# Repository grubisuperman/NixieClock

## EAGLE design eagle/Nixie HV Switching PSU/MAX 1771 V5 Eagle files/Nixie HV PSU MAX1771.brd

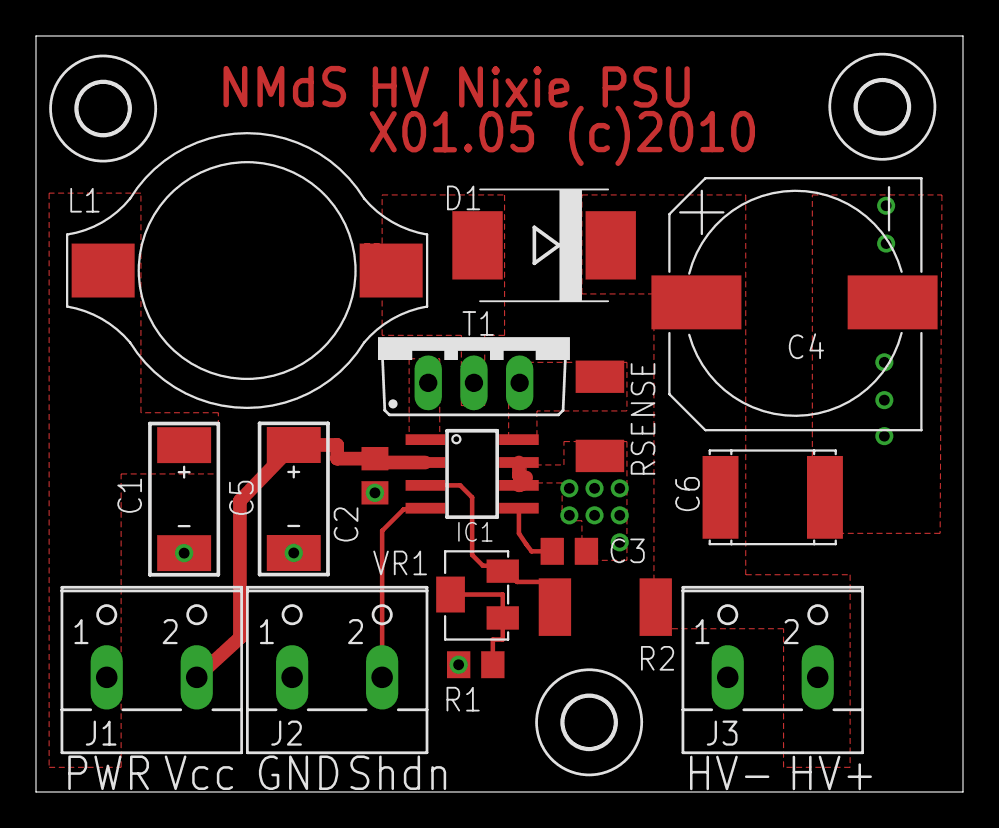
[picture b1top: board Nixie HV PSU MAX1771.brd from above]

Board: 2 copper layers, 51.5 x 42.0 mm, 20 parts (0 on the bottom side), 11 nets.

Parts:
C1: 100uF,35V; C-EIA-7343
C2, C3: 100n; C0805
C4: 4u7,250V; NICHICON-UJ-12
C5: 10uF,25V; C-EIA-7343
C6: 100n,250V; C2420
D1: ES2F; SMC
IC1: MAX1771ESA; SO-8
J1, J2, J3: SCREW-2-02
L1: 100uH; L-B82479
R1: 10K; R0805
R2: 1M5; R2512
RSENSE: 0R050; R2010
T1: IRF644PBF; TO220BV
U$2, U$3, U$4: 2,8
VR1: 5K; BOURNS-3214W

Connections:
DGND: C1.-, C2.2, C3.2, C4.1, C5.-, C6.P$2, IC1.6, IC1.7, J2.1, J3.1, R1.1, RSENSE.1
EXT: IC1.1, T1.G
unnamed: IC1.8, RSENSE.2, T1.S
unnamed: R1.2, VR1.1, VR1.2
unnamed: IC1.3, R2.1, VR1.3
unnamed: D1.A, L1.P$2, T1.D
unnamed: C3.1, IC1.5
PWR: C1.+, J1.1, L1.P$1
SHDN: IC1.4, J2.2
VCC: C2.1, C5.+, IC1.2, J1.2
VOUT: C4.2, C6.P$1, D1.C, J3.2, R2.2

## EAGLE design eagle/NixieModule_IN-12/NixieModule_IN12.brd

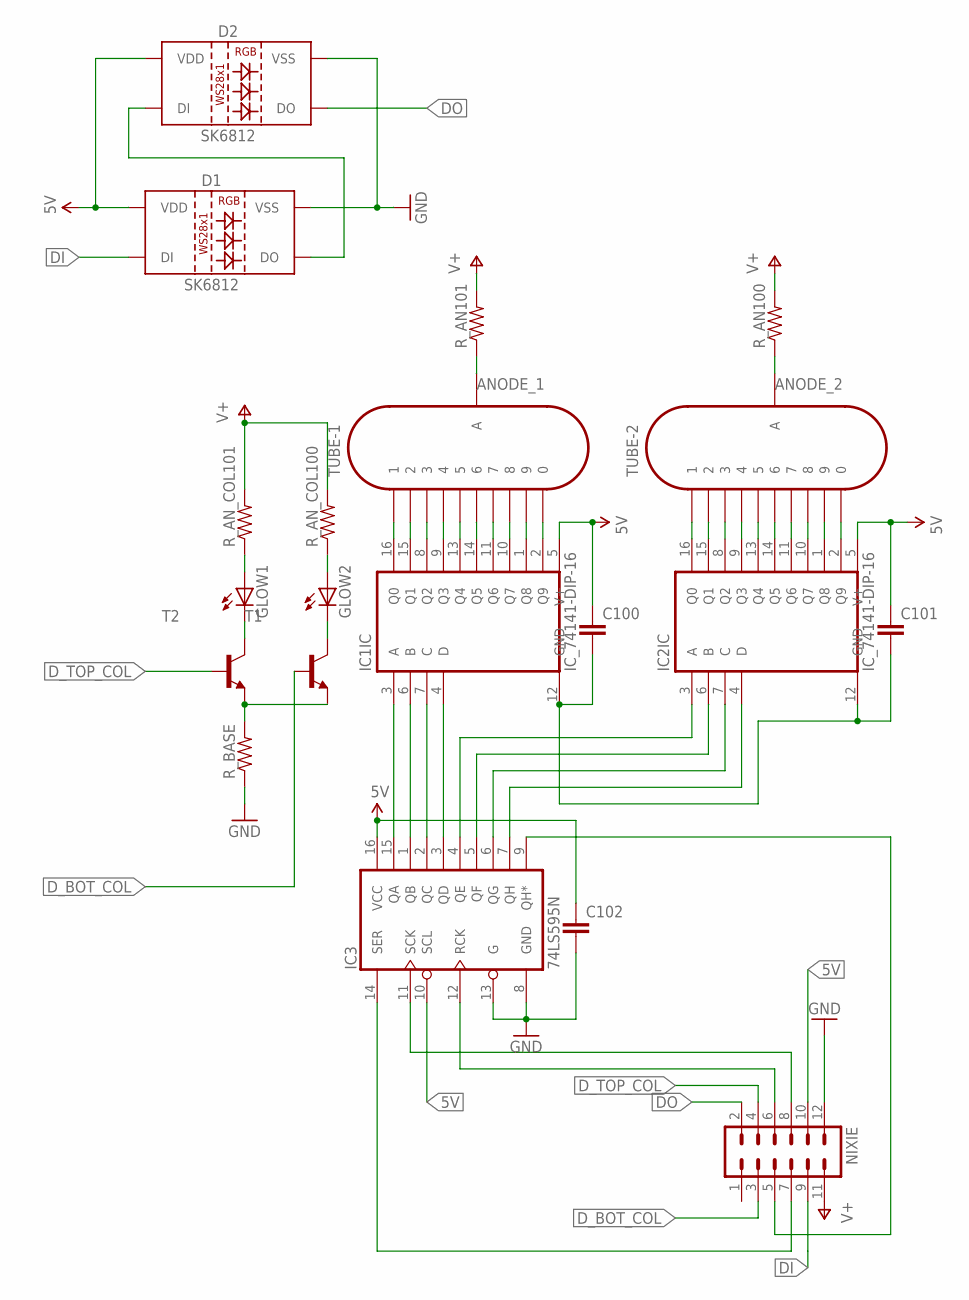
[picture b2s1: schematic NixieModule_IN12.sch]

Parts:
C100, C101, C102: C-EU050-024X044; C050-024X044
D1, D2: SK6812; WS2812B
GLOW1, GLOW2: LED_ELD260; LED_LD260
IC1, IC2: IC_74141-DIP-16; DIL16
IC3: 74LS595N; DIL16
NIXIE: MA06-2
R_AN100, R_AN101: RESISTORPTH-1/4W; AXIAL-0.4
R_AN_COL100, R_AN_COL101: RESISTORPTH-1/4W; AXIAL-0.4
R_BASE: RESISTORPTH-1/4W; AXIAL-0.4
T1, T2: -NPN-TO92-EBC; TO92-EBC
TUBE-1, TUBE-2: IN-12A; IN-12

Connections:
5V: C100.1, C101.1, C102.1, D1.1 (VDD), D2.1 (VDD), IC1.5 (V+), IC2.5 (V+), IC3.10 (SCL), IC3.16 (VCC), NIXIE.10
ANODE_1: R_AN101.P$1 (1), TUBE-1.A
ANODE_2: R_AN100.P$1 (1), TUBE-2.A
DI: D1.4 (DI), NIXIE.9
DO: D2.2 (DO), NIXIE.2
D_BOT_COL: NIXIE.3, T1.B
D_TOP_COL: NIXIE.4, T2.B
GND: C100.2, C101.2, C102.2, D1.3 (VSS), D2.3 (VSS), IC1.12 (GND), IC2.12 (GND), IC3.8 (GND), IC3.13 (G), NIXIE.12, R_BASE.P$1 (1)
unnamed: GLOW1.A, R_AN_COL101.P$1 (1)
unnamed: GLOW2.A, R_AN_COL100.P$1 (1)
unnamed: GLOW1.K (C), T2.C
unnamed: IC1.16 (Q0), TUBE-1.1
unnamed: IC1.15 (Q1), TUBE-1.2
unnamed: IC1.8 (Q2), TUBE-1.3
unnamed: IC1.9 (Q3), TUBE-1.4
unnamed: IC1.13 (Q4), TUBE-1.5
unnamed: IC1.14 (Q5), TUBE-1.6
unnamed: IC1.11 (Q6), TUBE-1.7
unnamed: IC1.10 (Q7), TUBE-1.8
unnamed: IC1.1 (Q8), TUBE-1.9
unnamed: IC1.2 (Q9), TUBE-1.0
unnamed: GLOW2.K (C), T1.C
unnamed: R_BASE.P$2 (2), T1.E, T2.E
unnamed: IC2.9 (Q3), TUBE-2.4
unnamed: IC2.13 (Q4), TUBE-2.5
unnamed: IC2.14 (Q5), TUBE-2.6
unnamed: IC2.11 (Q6), TUBE-2.7
unnamed: IC2.10 (Q7), TUBE-2.8
unnamed: IC2.1 (Q8), TUBE-2.9
unnamed: IC2.2 (Q9), TUBE-2.0
unnamed: D1.2 (DO), D2.4 (DI)
unnamed: IC1.6 (B), IC3.1 (QB)
unnamed: IC1.7 (C), IC3.2 (QC)
unnamed: IC1.4 (D), IC3.3 (QD)
unnamed: IC1.3 (A), IC3.15 (QA)
unnamed: IC2.3 (A), IC3.4 (QE)
unnamed: IC2.6 (B), IC3.5 (QF)
unnamed: IC2.7 (C), IC3.6 (QG)
unnamed: IC2.4 (D), IC3.7 (QH)
RCK: IC3.12 (RCK), NIXIE.6
SCK: IC3.11 (SCK), NIXIE.8
SERIAL_SHIFT_IN: IC3.14 (SER), NIXIE.7
SERIAL_SHIFT_OUT: IC3.9 (QH*), NIXIE.5
T2_1: IC2.16 (Q0), TUBE-2.1
T2_2: IC2.15 (Q1), TUBE-2.2
T2_3: IC2.8 (Q2), TUBE-2.3
V+: NIXIE.11, R_AN100.P$2 (2), R_AN101.P$2 (2), R_AN_COL100.P$2 (2), R_AN_COL101.P$2 (2)

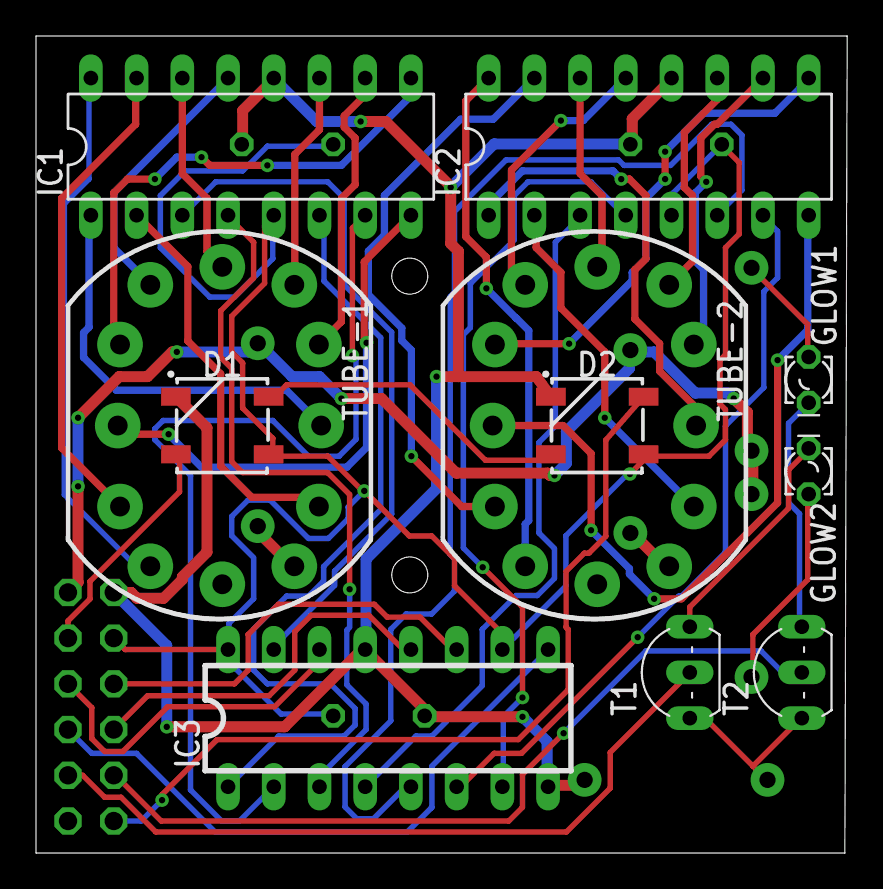
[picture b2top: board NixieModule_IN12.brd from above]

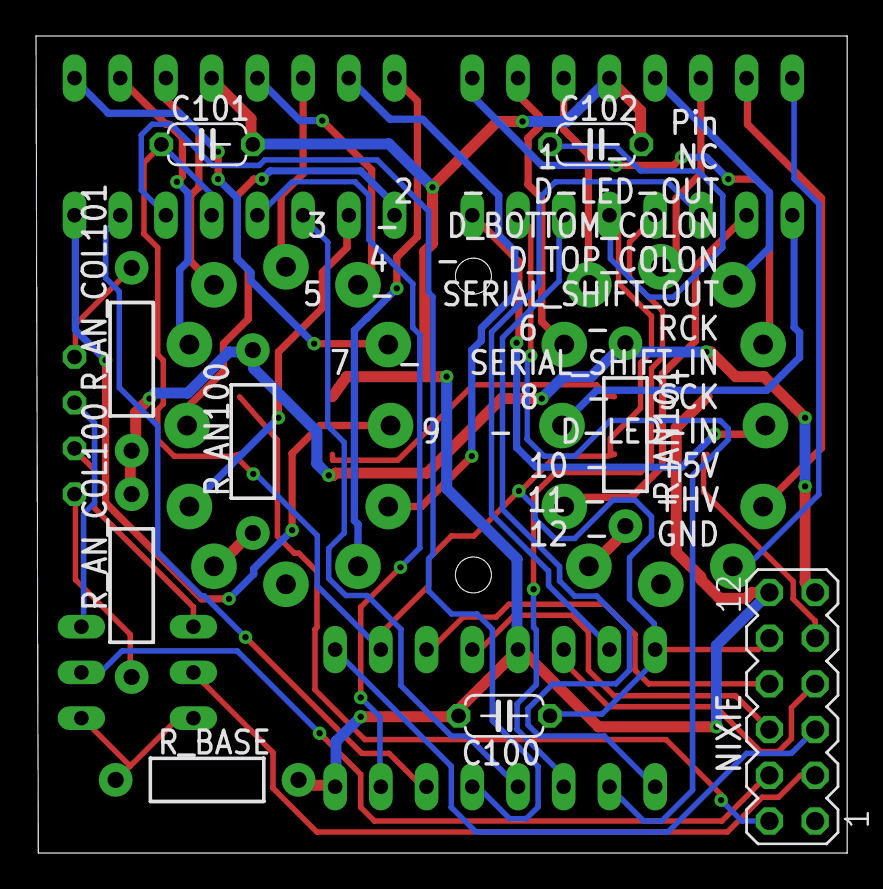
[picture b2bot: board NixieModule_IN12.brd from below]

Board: 2 copper layers, 45.1 x 45.4 mm, 20 parts (9 on the bottom side), 47 nets.

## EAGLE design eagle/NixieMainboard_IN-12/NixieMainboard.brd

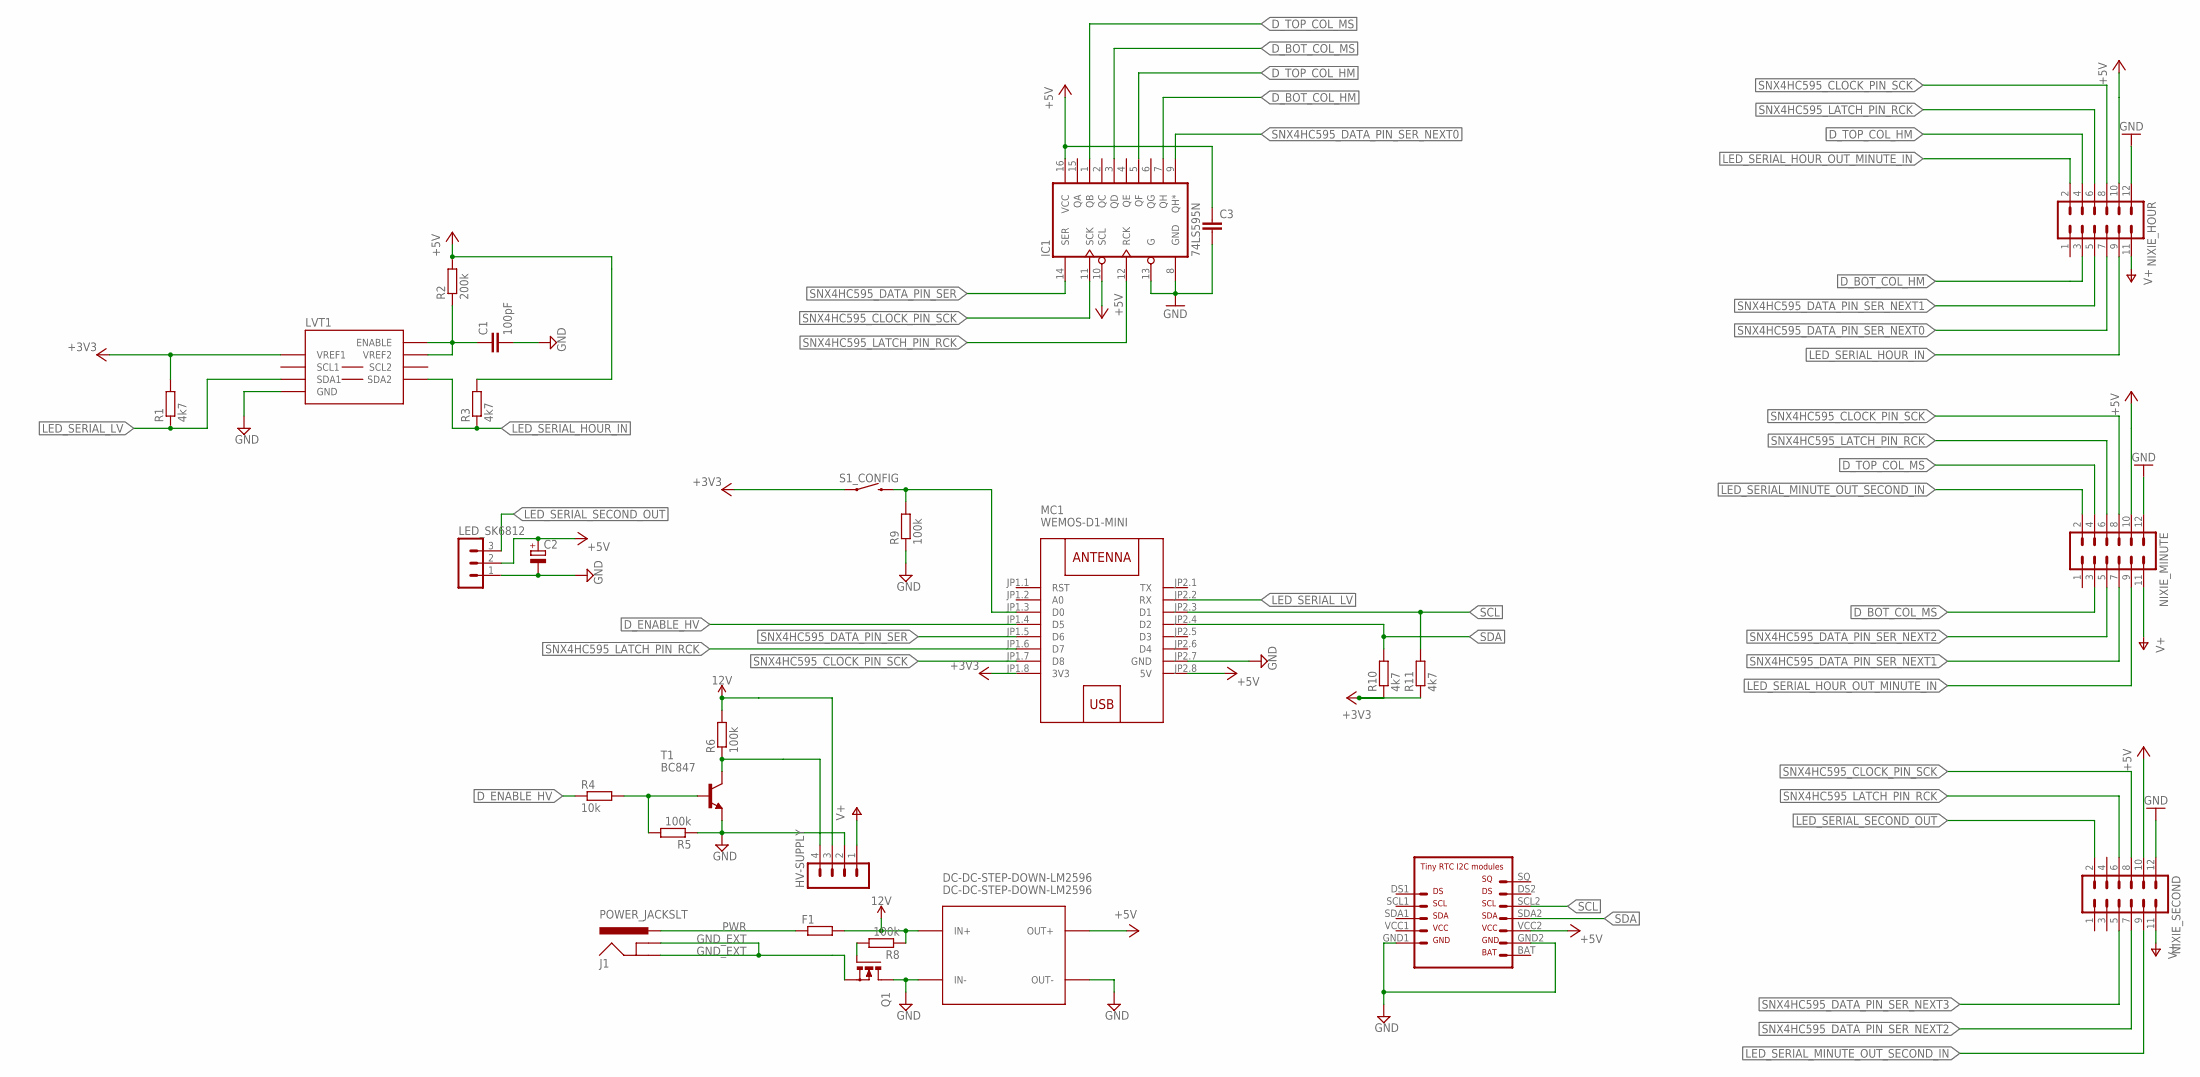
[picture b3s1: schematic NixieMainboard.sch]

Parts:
C1: 100pF; C0805
C2: CPOL-EUE5-8.5; E5-8,5
C3: C-EU050-024X044; C050-024X044
DC-DC-STEP-DOWN-LM2596: DC-DC-STEP-DOWN-LM2596
F1: R-EU_R2512W; R2512W
HV-SUPPLY: MA04-1
IC1: 74LS595N; DIL16
J1: POWER_JACKSLT; POWER_JACK_SLOT
LED_SK6812: MA03-1
LVT1: IC2_LEVEL_TRANSLATER; SOIC-8
MC1: WEMOS-D1-MINI
NIXIE_HOUR: MA06-2
NIXIE_MINUTE: MA06-2
NIXIE_SECOND: MA06-2
Q1: PMOSFET_NTO220BV; TO220BV
R1, R3, R10, R11: 4k7; R0805
R2: 200k; R0805
R4: 10k; R0805
R5, R6, R8, R9: 100k; R0805
RTC1: RTC
S1_CONFIG: MOMENTARY-SWITCH-SPST-PTH-6.0MM; TACTILE_SWITCH_PTH_6.0MM
T1: BC847; SOT23

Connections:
12V: DC-DC-STEP-DOWN-LM2596.IN+, F1.2, HV-SUPPLY.3, R6.2, R8.1
+3V3: LVT1.1 (VREF1), MC1.JP1.8 (3V3), R1.2, R10.1, R11.1, S1_CONFIG.1
+5V: C2.+, C3.1, DC-DC-STEP-DOWN-LM2596.OUT+, IC1.10 (SCL), IC1.16 (VCC), LED_SK6812.2, MC1.JP2.8 (5V), NIXIE_HOUR.10, NIXIE_MINUTE.10, NIXIE_SECOND.10, R2.2, R3.2, RTC1.VCC2
D_BOT_COL_HM: IC1.7 (QH), NIXIE_HOUR.3
D_BOT_COL_MS: IC1.3 (QD), NIXIE_MINUTE.3
D_ENABLE_HV: MC1.JP1.4 (D5), R4.1
D_TOP_COL_HM: IC1.5 (QF), NIXIE_HOUR.4
D_TOP_COL_MS: IC1.1 (QB), NIXIE_MINUTE.4
GND: C1.2, C2.-, C3.2, DC-DC-STEP-DOWN-LM2596.IN-, DC-DC-STEP-DOWN-LM2596.OUT-, HV-SUPPLY.2, IC1.8 (GND), IC1.13 (G), LED_SK6812.1, LVT1.4 (GND), MC1.JP2.7 (GND), NIXIE_HOUR.12, NIXIE_MINUTE.12, NIXIE_SECOND.12, Q1.D, R5.1, R9.1, RTC1.GND1, RTC1.GND2, T1.2 (E)
GND_EXT: J1.GND@1 (GNDBREAK), J1.GND@2 (GND), Q1.S
LED_SERIAL_HOUR_IN: LVT1.5 (SDA2), NIXIE_HOUR.9, R3.1
LED_SERIAL_HOUR_OUT_MINUTE_IN: NIXIE_HOUR.2, NIXIE_MINUTE.9
LED_SERIAL_LV: LVT1.3 (SDA1), MC1.JP2.2 (RX), R1.1
LED_SERIAL_MINUTE_OUT_SECOND_IN: NIXIE_MINUTE.2, NIXIE_SECOND.9
LED_SERIAL_SECOND_OUT: LED_SK6812.3, NIXIE_SECOND.2
unnamed: R4.2, R5.2, T1.1 (B)
unnamed: HV-SUPPLY.4, R6.1, T1.3 (C)
unnamed: Q1.G, R8.2
unnamed: MC1.JP1.3 (D0), R9.2, S1_CONFIG.3 (2)
unnamed: C1.1, LVT1.7 (VREF2), LVT1.8 (ENABLE), R2.1
PWR: F1.1, J1.PWR
SCL: MC1.JP2.3 (D1), R11.2, RTC1.SCL2
SDA: MC1.JP2.4 (D2), R10.2, RTC1.SDA2
SNX4HC595_CLOCK_PIN_SCK: IC1.11 (SCK), MC1.JP1.7 (D8), NIXIE_HOUR.8, NIXIE_MINUTE.8, NIXIE_SECOND.8
SNX4HC595_DATA_PIN_SER: IC1.14 (SER), MC1.JP1.5 (D6)
SNX4HC595_DATA_PIN_SER_NEXT0: IC1.9 (QH*), NIXIE_HOUR.7
SNX4HC595_DATA_PIN_SER_NEXT1: NIXIE_HOUR.5, NIXIE_MINUTE.7
SNX4HC595_DATA_PIN_SER_NEXT2: NIXIE_MINUTE.5, NIXIE_SECOND.7
SNX4HC595_DATA_PIN_SER_NEXT3: NIXIE_SECOND.5
SNX4HC595_LATCH_PIN_RCK: IC1.12 (RCK), MC1.JP1.6 (D7), NIXIE_HOUR.6, NIXIE_MINUTE.6, NIXIE_SECOND.6
V+: HV-SUPPLY.1, NIXIE_HOUR.11, NIXIE_MINUTE.11, NIXIE_SECOND.11

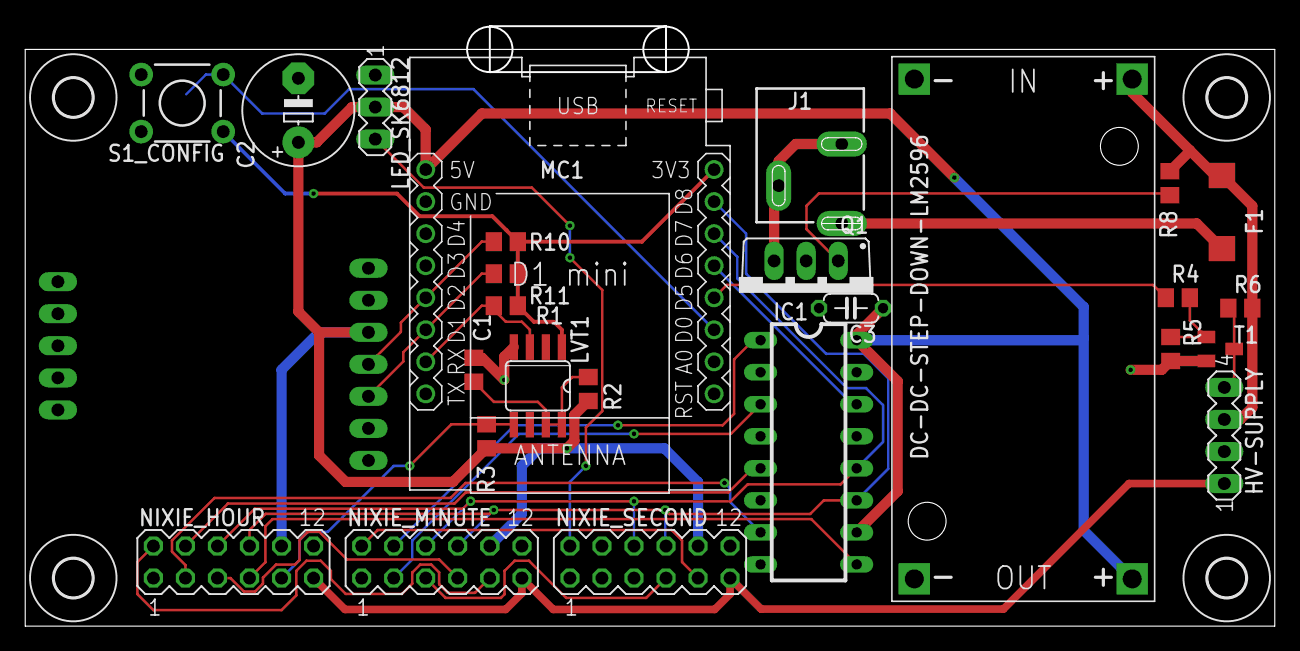
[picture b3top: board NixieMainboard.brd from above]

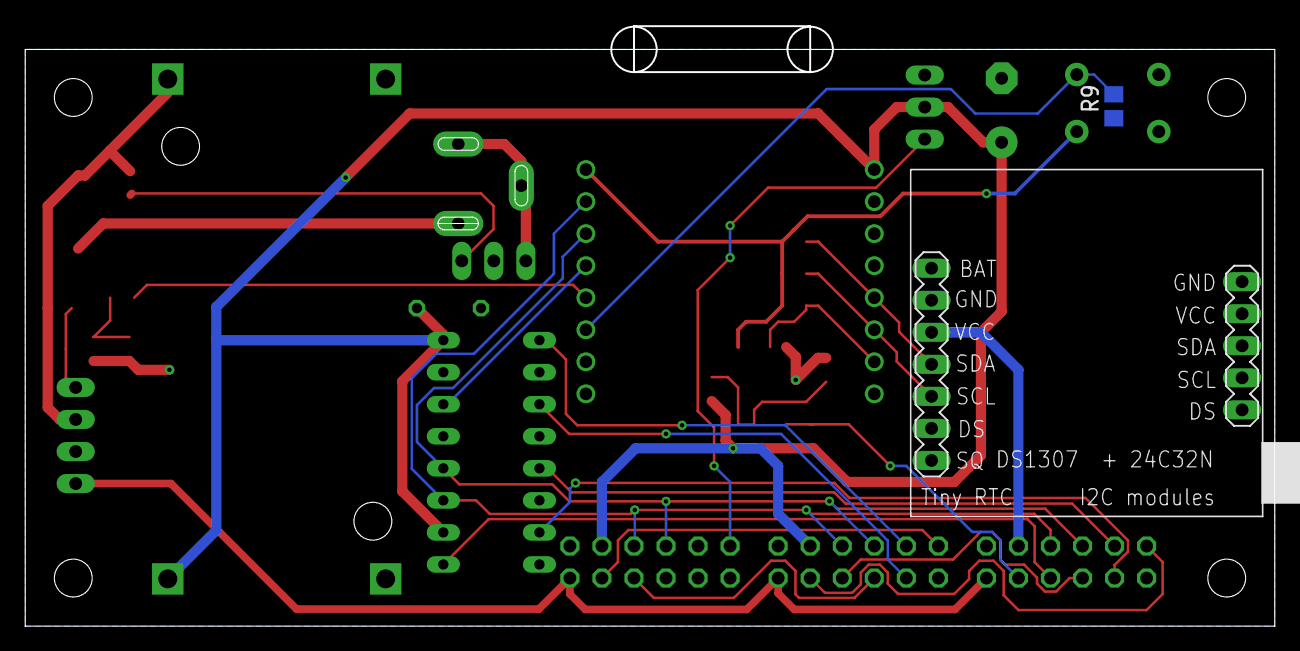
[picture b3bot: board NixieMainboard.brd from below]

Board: 2 copper layers, 98.9 x 47.5 mm, 32 parts (2 on the bottom side), 30 nets.

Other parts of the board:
U$2, U$3, U$4, U$5: 3,0

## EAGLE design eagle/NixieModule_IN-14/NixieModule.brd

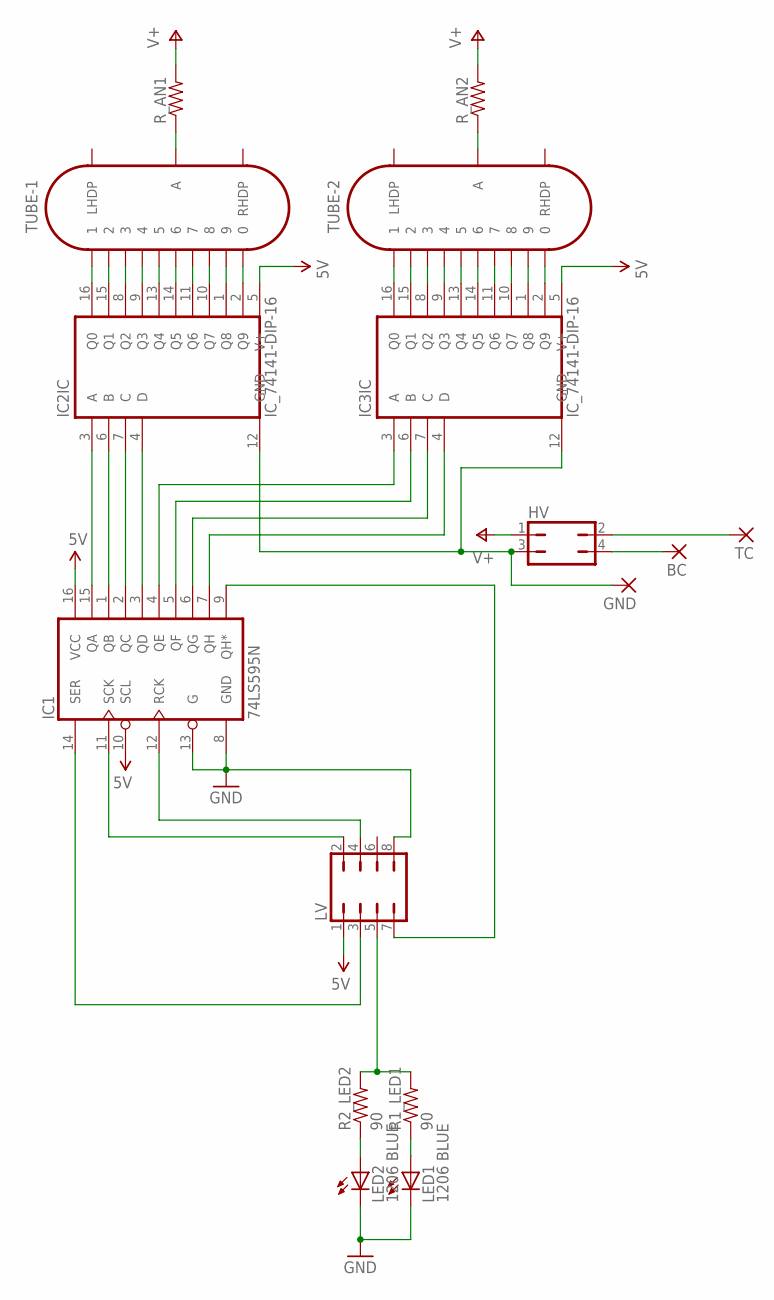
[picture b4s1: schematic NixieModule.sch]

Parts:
BC: 1,6/0,9
GND: 1,6/0,9
HV: JP2Q
IC1: 74LS595N; DIL16
IC2, IC3: IC_74141-DIP-16; DIL16
LED1, LED2: 1206 BLUE; LED_1206
LV: JP4Q
R1_LED1, R2_LED2: 90; AXIAL-0.4
R_AN1, R_AN2: RESISTORPTH-1/4W; AXIAL-0.4
TC: 1,6/0,9
TUBE-1, TUBE-2: IN-14

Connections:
5V: IC1.16 (VCC), IC2.5 (V+), IC3.5 (V+), LV.1
GND: GND.1, HV.3, IC1.8 (GND), IC1.13 (G), IC2.12 (GND), IC3.12 (GND), LED1.C, LED2.C, LV.8
unnamed: R_AN1.P$1 (1), TUBE-1.A
unnamed: R_AN2.P$1 (1), TUBE-2.A
unnamed: IC1.12 (RCK), LV.4
unnamed: IC1.11 (SCK), LV.2
unnamed: IC1.14 (SER), LV.3
unnamed: LED2.A, R2_LED2.P$1 (1)
unnamed: IC2.16 (Q0), TUBE-1.1
unnamed: IC2.15 (Q1), TUBE-1.2
unnamed: IC2.8 (Q2), TUBE-1.3
unnamed: IC2.9 (Q3), TUBE-1.4
unnamed: IC2.13 (Q4), TUBE-1.5
unnamed: IC2.14 (Q5), TUBE-1.6
unnamed: IC2.11 (Q6), TUBE-1.7
unnamed: IC2.10 (Q7), TUBE-1.8
unnamed: IC2.1 (Q8), TUBE-1.9
unnamed: IC2.2 (Q9), TUBE-1.0
unnamed: IC3.16 (Q0), TUBE-2.1
unnamed: IC3.15 (Q1), TUBE-2.2
unnamed: IC3.8 (Q2), TUBE-2.3
unnamed: IC3.9 (Q3), TUBE-2.4
unnamed: IC3.13 (Q4), TUBE-2.5
unnamed: IC3.14 (Q5), TUBE-2.6
unnamed: IC3.11 (Q6), TUBE-2.7
unnamed: IC3.10 (Q7), TUBE-2.8
unnamed: IC3.1 (Q8), TUBE-2.9
unnamed: IC3.2 (Q9), TUBE-2.0
unnamed: LED1.A, R1_LED1.P$1 (1)
unnamed: LV.5, R1_LED1.P$2 (2), R2_LED2.P$2 (2)
unnamed: HV.2, TC.1
unnamed: BC.1, HV.4
unnamed: IC1.1 (QB), IC2.6 (B)
unnamed: IC1.2 (QC), IC2.7 (C)
unnamed: IC1.3 (QD), IC2.4 (D)
unnamed: IC1.15 (QA), IC2.3 (A)
unnamed: IC1.4 (QE), IC3.3 (A)
unnamed: IC1.5 (QF), IC3.6 (B)
unnamed: IC1.6 (QG), IC3.7 (C)
unnamed: IC1.7 (QH), IC3.4 (D)
unnamed: IC1.9 (QH*), LV.7
V+: HV.1, R_AN1.P$2 (2), R_AN2.P$2 (2)
VCC: IC1.10 (SCL)

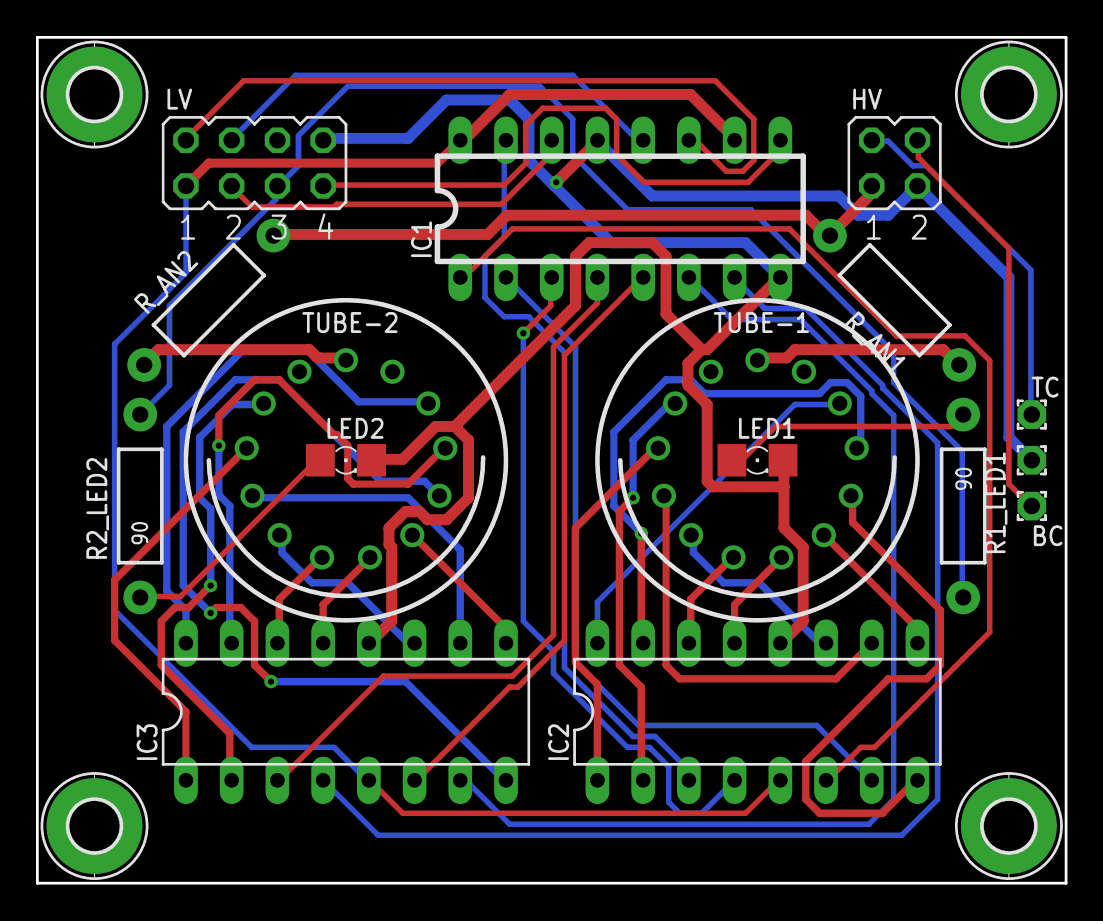
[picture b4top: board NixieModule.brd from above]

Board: 2 copper layers, 57.1 x 47.0 mm, 20 parts (0 on the bottom side), 42 nets.

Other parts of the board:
H1, H2, H3, H4: MOUNT-PAD-ROUND2.8; 2,8-PAD

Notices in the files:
eagle/Nixie HV Switching PSU/MAX 1771 V5 Eagle files/Nixie HV PSU MAX1771.brd:
(c)2010
parts and their libraries:
diy-modules: Released under the Creative Commons Attribution 4.0 International License: http://creativecommons.org/licenses/by/4.0
SparkFun-Connectors: Licensing: Creative Commons ShareAlike 4.0 International - https://creativecommons.org/licenses/by-sa/4.0
